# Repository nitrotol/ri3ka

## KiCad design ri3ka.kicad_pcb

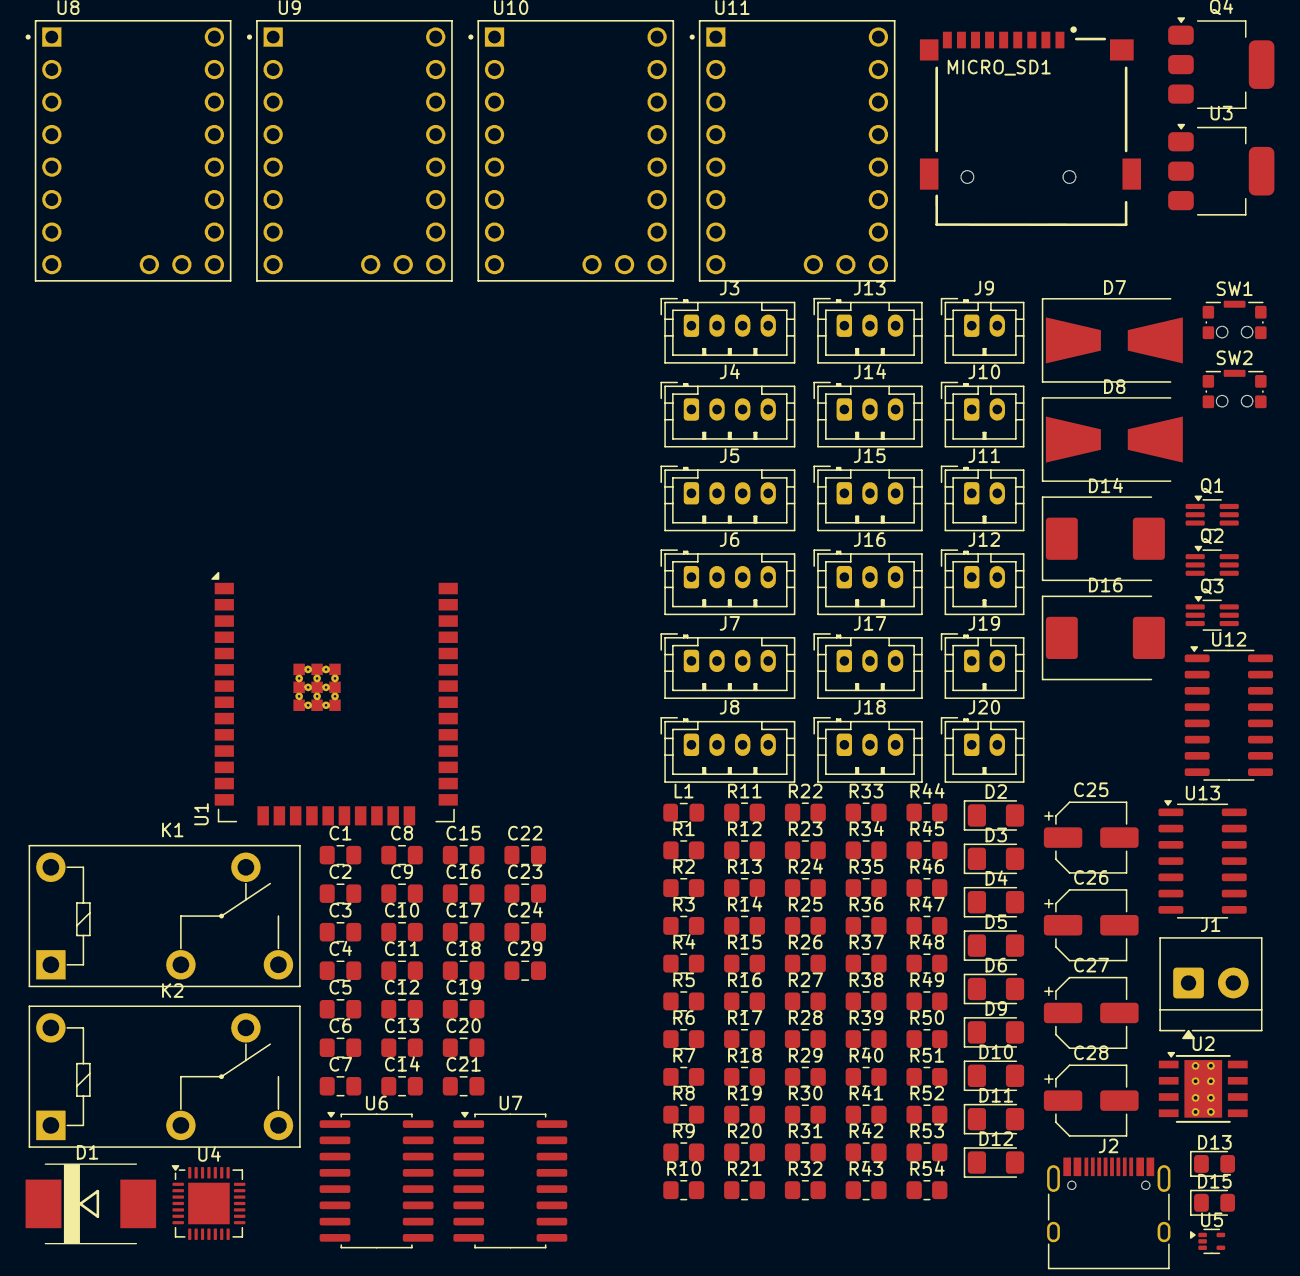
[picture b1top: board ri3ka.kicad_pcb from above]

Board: 2 copper layers, 142 parts (0 on the bottom side), 124 nets, no tracks yet.

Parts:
C1, C10, C11: 10uF; C_0805_2012Metric_Pad1.18x1.45mm_HandSolder
C2, C5, C12, C13, C14, C16, C18, C19, C20, C21, C22, C23, C24: 100nF; C_0805_2012Metric_Pad1.18x1.45mm_HandSolder
C3, C4: 2.2uF; C_0805_2012Metric_Pad1.18x1.45mm_HandSolder
C6: 39pF; C_0805_2012Metric_Pad1.18x1.45mm_HandSolder
C7: 6.8nF; C_0805_2012Metric_Pad1.18x1.45mm_HandSolder
C8, C9: 47uF; C_0805_2012Metric_Pad1.18x1.45mm_HandSolder
C15, C17: 10nF; C_0805_2012Metric_Pad1.18x1.45mm_HandSolder
C25, C26, C27, C28: 300uF; CP_Elec_5x3
C29: C; C_0805_2012Metric_Pad1.18x1.45mm_HandSolder
D1: B560C-13-F; SMC
D2, D3, D4, D5, D6, D9, D10, D11, D12: LED; LED_1206_3216Metric_Pad1.42x1.75mm_HandSolder
D7, D8: B340; D_SMB-SMC_Universal_Handsoldering
D13, D15: LED; LED_0805_2012Metric_Pad1.15x1.40mm_HandSolder
D14, D16: B340; D_SMC
J1: Screw_Terminal_01x02; TerminalBlock_4Ucon_1x02_P3.50mm_Horizontal
J2: USB_C_Receptacle_USB2.0_14P; USB_C_Receptacle_HRO_TYPE-C-31-M-12
J3: MOT_XA; JST_PH_B4B-PH-K_1x04_P2.00mm_Vertical
J4: MOT_YA; JST_PH_B4B-PH-K_1x04_P2.00mm_Vertical
J5: MOT_Z; JST_PH_B4B-PH-K_1x04_P2.00mm_Vertical
J6: MOT_A; JST_PH_B4B-PH-K_1x04_P2.00mm_Vertical
J7: MOT_YB; JST_PH_B4B-PH-K_1x04_P2.00mm_Vertical
J8: MOT_XB; JST_PH_B4B-PH-K_1x04_P2.00mm_Vertical
J9, J10, J11, J12: Conn_01x02_Socket; JST_PH_B2B-PH-K_1x02_P2.00mm_Vertical
J13, J14, J15, J16, J17, J18: Conn_01x03_Pin; JST_PH_B3B-PH-K_1x03_P2.00mm_Vertical
J19, J20: Conn_01x02_Pin; JST_PH_B2B-PH-K_1x02_P2.00mm_Vertical
K1, K2: Relay_SPDT; Relay_SPDT_Omron-G5Q-1
L1: 10uH; L_0805_2012Metric_Pad1.15x1.40mm_HandSolder
MICRO_SD1: TF-01A
Q1, Q2, Q3: PMBT3904YS; SOT-363_SC-70-6_Handsoldering
Q4: FDS4559; SOT-223-3_TabPin2
R1: 100k; R_0805_2012Metric_Pad1.20x1.40mm_HandSolder
R2: 13k; R_0805_2012Metric_Pad1.20x1.40mm_HandSolder
R3: 270k; R_0805_2012Metric_Pad1.20x1.40mm_HandSolder
R4: 51k; R_0805_2012Metric_Pad1.20x1.40mm_HandSolder
R5, R27, R28, R29, R30, R37, R38, R39, R40: 6.8k; R_0805_2012Metric_Pad1.20x1.40mm_HandSolder
R6, R7, R51, R52, R53, R54: R; R_0805_2012Metric_Pad1.20x1.40mm_HandSolder
R8, R11, R12, R15, R17, R20, R21, R22, R23, R24, R25, R26, R32, R42, R44, R46, R48: 10k; R_0805_2012Metric_Pad1.20x1.40mm_HandSolder
R9, R10, R13, R14, R16, R31, R41, R43, R45, R47, R49, R50: 1k; R_0805_2012Metric_Pad1.20x1.40mm_HandSolder
R18, R19: 5.1k; R_0805_2012Metric_Pad1.20x1.40mm_HandSolder
R33, R34, R35, R36: 300; R_0805_2012Metric_Pad1.20x1.40mm_HandSolder
SW1: Reset; SW_SPST_CK_KMS2xxGP
SW2: Boot; SW_SPST_CK_KMS2xxGP
U1: ESP32-WROOM-32E
U2: TPS54360DDA; TI_SO-PowerPAD-8_ThermalVias
U3: AMS1117-3.3; SOT-223-3_TabPin2
U4: CP2102N-Axx-xQFN28; QFN-28-1EP_5x5mm_P0.5mm_EP3.25x3.25mm
U5: TPD3E001DRLR; SOT-553
U6, U7: 74AHCT595; SOIC-16W_5.3x10.2mm_P1.27mm
U8: DRV_X; MODULE_TMC2209_SILENTSTEPSTICK
U9: DRV_Y; MODULE_TMC2209_SILENTSTEPSTICK
U10: DRV_Z; MODULE_TMC2209_SILENTSTEPSTICK
U11: DRV_A; MODULE_TMC2209_SILENTSTEPSTICK
U12: TLP521-4; SOIC-16_3.9x9.9mm_P1.27mm
U13: 74AHCT125; SOIC-14_3.9x8.7mm_P1.27mm

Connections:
+3.3V: C1.1, C2.1, C11.1, C12.1, C15.1, C16.1, MICRO_SD1.4 (VDD), R8.1, R11.1, R12.1, R15.1, R17.1, R23.1, R24.1, R25.1, R26.1, R32.1, U1.2 (VDD), U3.2 (VO), U4.6 (VDD), U4.7 (VREGIN), U8.2 (VIO), U9.2 (VIO), U10.2 (VIO), U11.2 (VIO)
+5V: C8.1, C9.1, C10.1, C19.1, C20.1, C22.1, C23.1, C24.1, C29.1, D2.2 (A), D7.1 (K), D8.1 (K), L1.2, R3.1, R22.1, U3.3 (VI), U6.16 (VCC), U7.16 (VCC), U12.1, U12.3, U12.5, U12.7, U13.14 (VCC)
AHCT2: U6.9 (QH'), U7.14 (SER)
A_CS: U7.6 (QG), U11.13 (CS)
A_DIAG: R24.2, U1.4 (SENSOR_VP), U11.18 (DIAG1)
A_DIR: U7.4 (QE), U11.9 (DIR)
A_EN: U7.7 (QH), U11.16 (~EN)
A_SETP: R30.1, U11.10 (STEP)
DTR: Q1.4 (E2), R6.1, U4.28 (~DTR)
ESP_EN: C13.1, Q1.6 (C1), R8.2, SW1.2, U1.3 (EN)
GND: C1.2, C2.2, C3.2, C4.2, C6.2, C7.2, C8.2, C9.2, C10.2, C11.2, C12.2, C13.2, C14.2, C15.2, C16.2, C17.2, C18.2, C19.2, C20.2, C21.2, C22.2, C23.2, C24.2, C25.2, C26.2, C27.2, C28.2, C29.2, D1.A, D9.1 (K), D10.1 (K), D11.1 (K), D12.1 (K), D13.1 (K), D15.1 (K), J1.1, J2.A1 (GND), J2.A12 (GND), J2.B1 (GND), J2.B12 (GND), J2.S1 (SHIELD), J13.2, J14.2, J15.2, J16.2, MICRO_SD1.6 (VSS), MICRO_SD1.MP1 (SHIELD), MICRO_SD1.MP2 (SHIELD), MICRO_SD1.MP3 (SHIELD), MICRO_SD1.MP4 (SHIELD), Q2.4 (E2), Q3.4 (E2), Q4.1 (S1), Q4.3 (S2), R1.2, R4.2, R5.2, R9.2, R10.2, R18.2, R19.2, R20.2, R21.2, R37.1, R38.1, R39.1, R40.1, R42.1, R44.1, R46.1, R48.1, SW1.SH (B), SW2.SH (B), U1.1 (GND), U1.15 (GND), U1.38 (GND), U1.39 (GND), U2.7 (GND), U2.9 (GNDPAD), U3.1 (GND), U4.3 (GND), U4.29 (GND), U5.3, U6.8 (GND), U6.13 (~OE), U7.8 (GND), U7.13 (~OE), U8.1 (GND), U8.7 (GND), U9.1 (GND), U9.7 (GND), U10.1 (GND), U10.7 (GND), U11.1 (GND), U11.7 (GND), U12.9, U12.11, U12.13, U12.15, U13.1, U13.4, U13.7 (GND), U13.10, U13.13
GPIO0: C14.1, Q1.3 (C2), R11.2, SW2.2
I2S_BCK: R20.1, R21.1, U1.36 (IO22), U6.11 (SRCLK), U7.11 (SRCLK)
I2S_DATA: U1.33 (IO21), U6.14 (SER)
I2S_MR: C21.1, R22.2, U6.10 (~SRCLR), U7.10 (~SRCLR)
I2S_WS: U1.28 (IO17), U6.12 (RCLK), U7.12 (RCLK)
IN_1: R12.2, R13.2, U1.25 (IO0)
IN_2: R14.2, R15.2, U1.24 (IO2)
IN_3: R16.2, R17.2, U1.26 (IO4)
IN_4: R31.2, R32.2, U1.14 (IO12)
MISO: MICRO_SD1.7 (DAT0), U1.31 (IO19), U8.12 (SDO), U9.12 (SDO), U10.12 (SDO), U11.12 (SDO)
MOSI: MICRO_SD1.3 (CMD), U1.37 (IO23), U8.15 (SDI), U9.15 (SDI), U10.15 (SDI), U11.15 (SDI)
unnamed: C7.1, R2.2
unnamed: D2.1 (K), R5.1
unnamed: D3.2 (A), J9.2
unnamed: D3.1 (K), R37.2
unnamed: D4.2 (A), J10.2
unnamed: D4.1 (K), R38.2
unnamed: D5.2 (A), J11.2
unnamed: D5.1 (K), R39.2
unnamed: D6.2 (A), J12.2
unnamed: D6.1 (K), R40.2
unnamed: D7.2 (A), Q2.3 (C2)
unnamed: D8.2 (A), Q3.3 (C2)
unnamed: D9.2 (A), R27.2
unnamed: D10.2 (A), R28.2
unnamed: D11.2 (A), R29.2
unnamed: D12.2 (A), R30.2
unnamed: D13.2 (A), R51.2
unnamed: D14.2 (A), J19.1
unnamed: D15.2 (A), R53.2
unnamed: D16.2 (A), J20.1
unnamed: J2.A5 (CC1), R19.1
unnamed: J2.B5 (CC2), R18.1
unnamed: J3.1, J8.2, U8.4 (M1A)
unnamed: J3.2, J8.1, U8.5 (M2A)
unnamed: J3.3, J8.3, U8.3 (M1B)
unnamed: J3.4, J8.4, U8.6 (M2B)
unnamed: J4.1, J7.2, U9.4 (M1A)
unnamed: J4.2, J7.1, U9.5 (M2A)
unnamed: J4.3, J7.3, U9.3 (M1B)
unnamed: J4.4, J7.4, U9.6 (M2B)
unnamed: J5.1, U10.4 (M1A)
unnamed: J5.2, U10.5 (M2A)
unnamed: J5.3, U10.3 (M1B)
unnamed: J5.4, U10.6 (M2B)
unnamed: J6.1, U11.4 (M1A)
unnamed: J6.2, U11.5 (M2A)
unnamed: J6.3, U11.3 (M1B)
unnamed: J6.4, U11.6 (M2B)
unnamed: J9.1, R33.1
unnamed: J10.1, R34.1
unnamed: J11.1, R35.1
unnamed: J12.1, R36.1
unnamed: J13.3, U13.3
unnamed: J14.3, U13.6
unnamed: J15.3, U13.8
unnamed: J16.3, U13.11
unnamed: Q1.2 (B1), R6.2
unnamed: Q1.5 (B2), R7.2
unnamed: Q2.5 (B2), R49.2
unnamed: Q3.5 (B2), R50.2
unnamed: Q4.2 (G1), R52.2
unnamed: R9.1, SW1.1
unnamed: R10.1, SW2.1
unnamed: R13.1, U12.16
unnamed: R14.1, U12.14
unnamed: R16.1, U12.12
unnamed: R31.1, U12.10
unnamed: R33.2, U12.2
unnamed: R34.2, U12.4
unnamed: R35.2, U12.6
unnamed: R36.2, U12.8
unnamed: R41.2, R42.2, U13.2
unnamed: R43.2, R44.2, U13.5
unnamed: R45.2, R46.2, U13.9
unnamed: R47.2, R48.2, U13.12
unnamed: C5.1, U2.1 (BOOT)
unnamed: C6.1, R2.1, U2.6 (COMP)
unnamed: R3.2, R4.1, U2.5 (FB)
unnamed: R1.1, U2.4 (RT/CLK)
unnamed: C5.2, D1.C, L1.1, U2.8 (SW)
unnamed: J2.A6 (D+), J2.B6 (D+), U4.4 (D+), U5.2 (IO2)
unnamed: J2.A7 (D-), J2.B7 (D-), U4.5 (D-), U5.1 (IO1)
PWM_1: R41.1, U1.16 (IO13)
PWM_2: R43.1, U1.13 (IO14)
PWM_3: R45.1, U1.23 (IO15)
PWM_4: R47.1, U1.27 (IO16)
RELAY1: R49.1, U1.9 (IO33)
RELAY2: R50.1, U1.8 (IO32)
RST: Q1.1 (E1), R7.1, U4.24 (~RTS)
RX0: U1.34 (RXD0/IO3), U4.25 (RXD)
SCK: MICRO_SD1.5 (CLK), U1.30 (IO18), U8.14 (SCK), U9.14 (SCK), U10.14 (SCK), U11.14 (SCK)
SD_CS: MICRO_SD1.2 (CD/DAT3), U1.29 (IO5)
SW1: R51.1, R52.1, U1.12 (IO27)
SW2: R53.1, R54.1, U1.11 (IO26)
TX0: U1.35 (TXD0/IO1), U4.26 (TXD)
VBUS: C17.1, C18.1, J2.A4 (VBUS), J2.A9 (VBUS), J2.B4 (VBUS), J2.B9 (VBUS), U4.8 (VBUS), U5.5
VDC: C3.1, C4.1, C25.1, C26.1, C27.1, C28.1, D14.1 (K), D16.1 (K), J1.2, J13.1, J14.1, J15.1, J16.1, J19.2, J20.2, U2.2 (VIN), U8.8 (VM), U9.8 (VM), U10.8 (VM), U11.8 (VM)
X_CS: U6.3 (QD), U8.13 (CS)
X_DIAG: R26.2, U1.6 (IO34), U8.18 (DIAG1)
X_DIR: U6.1 (QB), U8.9 (DIR)
X_EN: U6.15 (QA), U8.16 (~EN)
X_SETP: R27.1, U6.2 (QC), U8.10 (STEP)
Y_CS: U6.6 (QG), U9.13 (CS)
Y_DIAG: R25.2, U1.7 (IO35), U9.18 (DIAG1)
Y_DIR: U6.4 (QE), U9.9 (DIR)
Y_EN: U6.7 (QH), U9.16 (~EN)
Y_SETP: R28.1, U9.10 (STEP)
Z_CS: U7.3 (QD), U10.13 (CS)
Z_DIAG: R23.2, U1.5 (SENSOR_VN), U10.18 (DIAG1)
Z_DIR: U7.1 (QB), U10.9 (DIR)
Z_EN: U7.15 (QA), U10.16 (~EN)
Z_SETP: R29.1, U10.10 (STEP)

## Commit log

2025-06-07 initial
2025-06-12 schematics ready
2025-06-12 board preparation
